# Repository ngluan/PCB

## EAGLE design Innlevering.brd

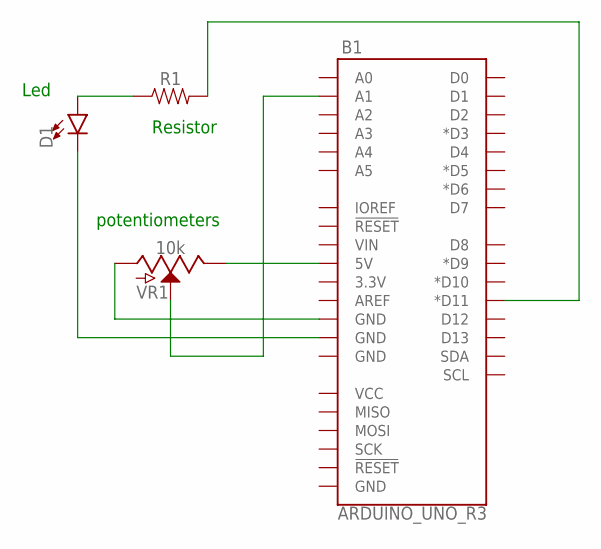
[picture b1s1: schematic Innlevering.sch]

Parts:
B1: ARDUINO_UNO_R3; ARDUINO_R3
D1: LED-3MM-NO_SILK; LED_3MM-NS
R1: AXIAL-0.3
VR1: 10k; POT-PTH-ALPS

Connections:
unnamed: B1.5V, VR1.P$1 (E)
unnamed: B1.A1, VR1.P$2 (S)
unnamed: B1.GND@4 (GND), VR1.P$3 (A)
unnamed: B1.GND@3 (GND), D1.K (C)
unnamed: D1.A, R1.P$1 (1)
unnamed: B1.D11 (*D11), R1.P$2 (2)

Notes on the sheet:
potentiometers
Resistor
Led

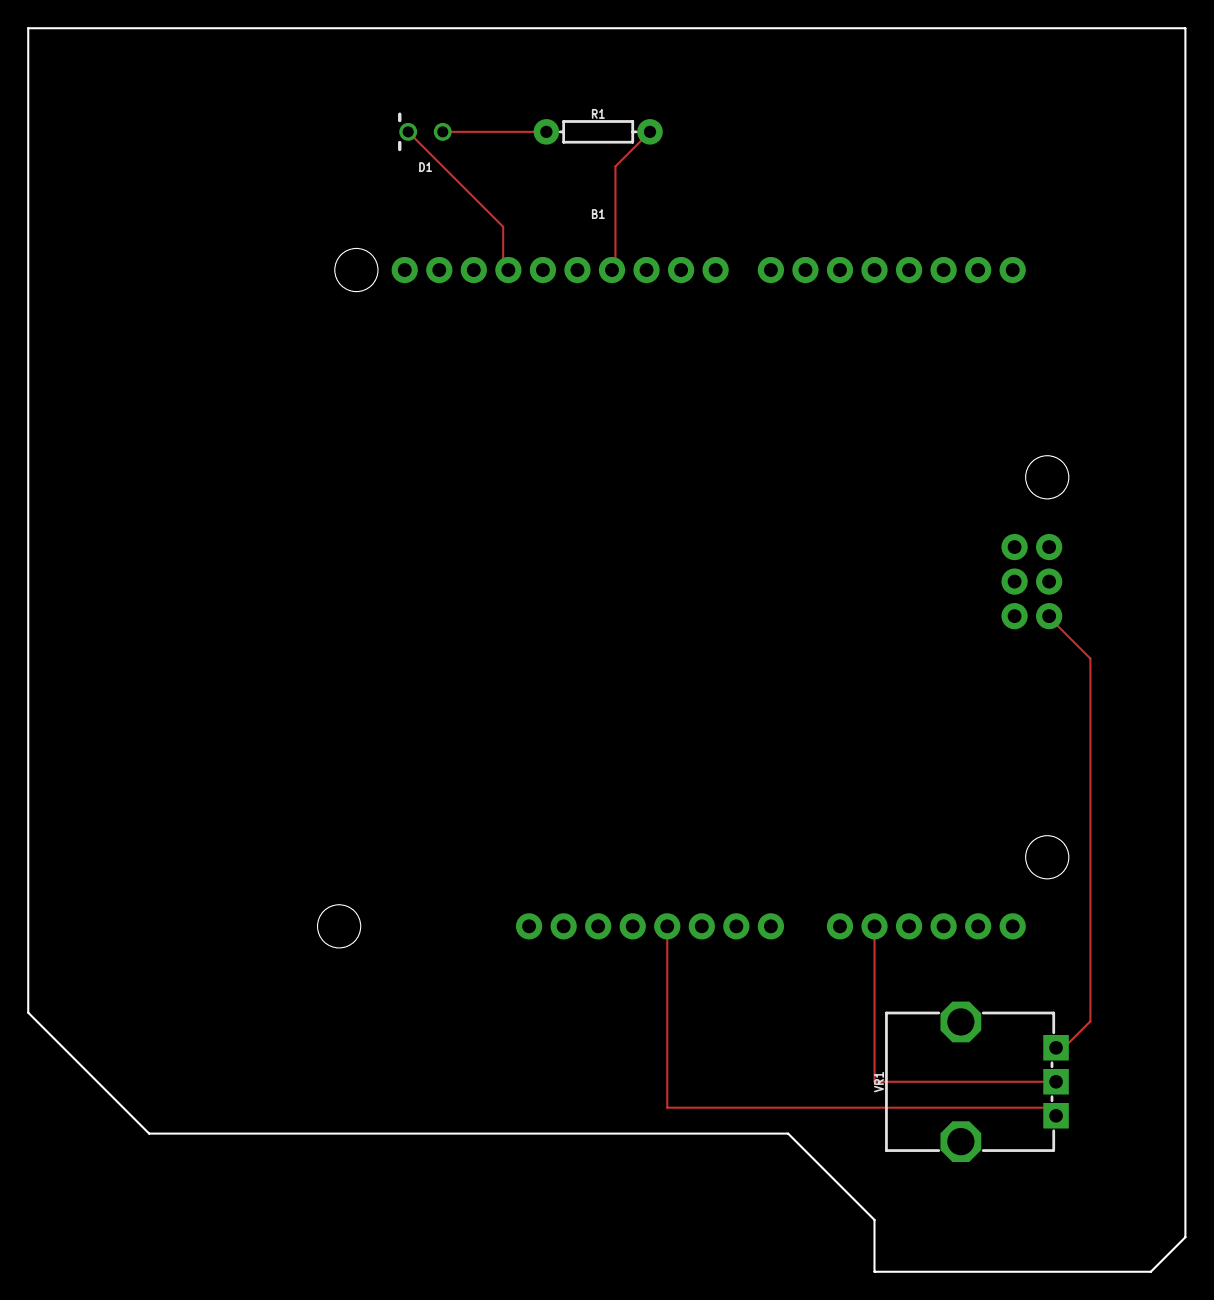
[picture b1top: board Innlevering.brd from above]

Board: 2 copper layers, 85.1 x 91.4 mm, 4 parts (0 on the bottom side), 6 nets.

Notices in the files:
parts and their libraries:
SparkFun-Boards: Licensing: Creative Commons ShareAlike 4.0 International - https://creativecommons.org/licenses/by-sa/4.0
